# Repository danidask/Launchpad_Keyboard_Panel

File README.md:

# Specifications

- Size limit to the biggest size of low cost PCB manufacturers entry point PCBs (jlcpcb 100x100mm)
- Most of the components will be selected from https://jlcpcb.com/parts so they can be assembly by JLCPCB
- Other components will be sourced from cheap worldwide providers like aliexpress

See READMEs inside each folder

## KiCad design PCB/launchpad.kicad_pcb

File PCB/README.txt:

(see parent README.md)

# Requirements

Made with KiCad 6

## KiCad Plugins

https://github.com/bouni/kicad-jlcpcb-tools

# Track changes

[cadlab.io](https://cadlab.io/project/25849/)

# Specifications

(see parent README.md)

# Fabrication

The PCB is intended to be manufactured by JLCPCB so the outputs meet they requirements. Necessary files for manufacturing and assembly are in the jlcpcb folder

# BOM

LCSC parts are inside PCB\jlcpcb\assembly (to be assembly by jlcpcb or sourced from there and solder them manually)
- 12x Kailh choc Low profile Mechanical Switch, https://a.aliexpress.com/_uHRL47  (10 or 70)
- 12x Keycaps for Kailh choc, https://a.aliexpress.com/_uGXK51 (transparent-choc)
- 1x SSD1306 38x12mm OLED Display, https://a.aliexpress.com/_vNfBEr
- 1x RaspberryPi Pico, https://www.raspberrypi.com/products/raspberry-pi-pico/

# TODO

- Cover vias with soldermask
- Add diodes or limit resistors to keyboard matrix
- Power planes for 3.3v and 5v
- all pots (R1, R2, R3) swap GND and 3,3

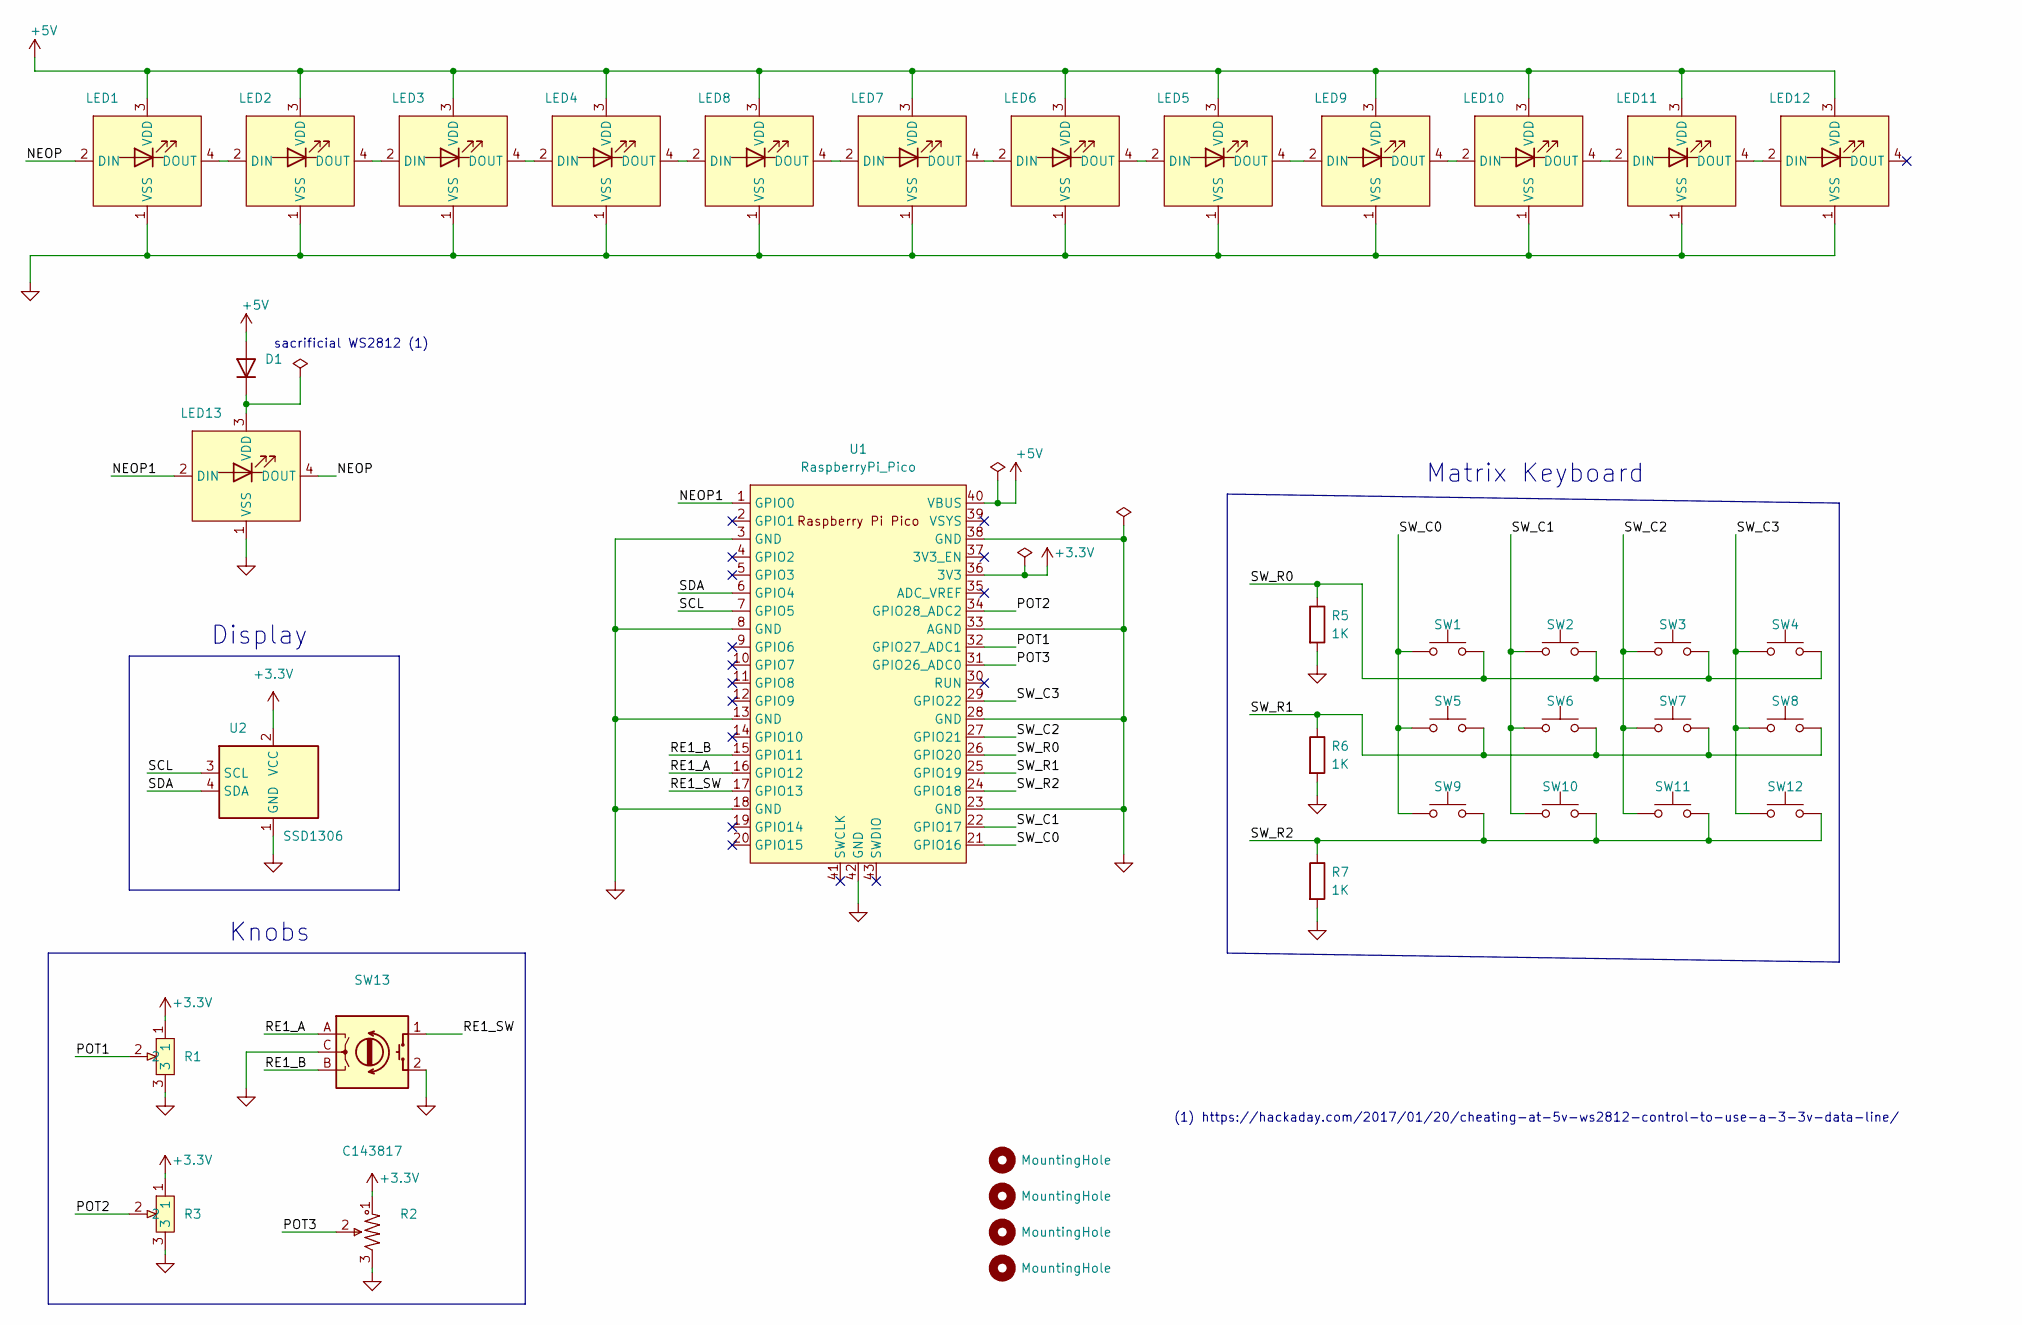
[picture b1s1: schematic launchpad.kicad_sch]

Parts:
D1: D; D_SOD-123F; MPN SM4007PL; LCSC C64898
H1, H2, H3, H4: MountingHole; MountingHole_3.2mm_M3
LED1, LED2, LED3, LED4, LED5, LED6, LED7, LED8, LED9, LED10, LED11, LED12, LED13: XL-3528RGBW-WS2812B; LED-SMD_4P-L3.5-W2.8-BR-1; LCSC Part C2890364
R1, R3: RDC1022A05; RES-ADJ-TH_RDC1022A05; LCSC Part C202389
R2: RK09K1130A6S; RES-TH_RK09K1130A6S; LCSC Part C209770
R5, R6, R7: 1K; R_0805_2012Metric_Pad1.20x1.40mm_HandSolder
SW1, SW2, SW3, SW4, SW5, SW6, SW7, SW8, SW9, SW10, SW11, SW12: Kaihua PG1350; Kaihua_PG1350
SW13: PEC11R-4220F-S0012; SW-TH_PEC11R-4220F-S0012; LCSC Part C143817
U1: RaspberryPi_Pico; RaspberryPi_Pico_SMD_TH
U2: SSD1306; SSD1306_38x12

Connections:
+3V3: R1.1, R2.1, R3.1, U1.36 (3V3), U2.2 (VCC)
+5V: D1.2 (A), LED1.3 (VDD), LED2.3 (VDD), LED3.3 (VDD), LED4.3 (VDD), LED5.3 (VDD), LED6.3 (VDD), LED7.3 (VDD), LED8.3 (VDD), LED9.3 (VDD), LED10.3 (VDD), LED11.3 (VDD), LED12.3 (VDD), U1.40 (VBUS)
/NEOP: LED1.2 (DIN), LED13.4 (DOUT)
/NEOP1: LED13.2 (DIN), U1.1 (GPIO0)
/POT1: R1.2, U1.32 (GPIO27_ADC1)
/POT2: R3.2, U1.34 (GPIO28_ADC2)
/POT3: R2.2, U1.31 (GPIO26_ADC0)
/RE1_A: SW13.A, U1.16 (GPIO12)
/RE1_B: SW13.B, U1.15 (GPIO11)
/RE1_SW: SW13.1 (S1), U1.17 (GPIO13)
/SCL: U1.7 (GPIO5), U2.3 (SCL)
/SDA: U1.6 (GPIO4), U2.4 (SDA)
/SW_C0: SW1.1 (A), SW5.1 (A), SW9.1 (A), U1.21 (GPIO16)
/SW_C1: SW2.1 (A), SW6.1 (A), SW10.1 (A), U1.22 (GPIO17)
/SW_C2: SW3.1 (A), SW7.1 (A), SW11.1 (A), U1.27 (GPIO21)
/SW_C3: SW4.1 (A), SW8.1 (A), SW12.1 (A), U1.29 (GPIO22)
/SW_R0: R5.1, SW1.2 (B), SW2.2 (B), SW3.2 (B), SW4.2 (B), U1.26 (GPIO20)
/SW_R1: R6.1, SW5.2 (B), SW6.2 (B), SW7.2 (B), SW8.2 (B), U1.25 (GPIO19)
/SW_R2: R7.1, SW9.2 (B), SW10.2 (B), SW11.2 (B), SW12.2 (B), U1.24 (GPIO18)
GND: LED1.1 (VSS), LED2.1 (VSS), LED3.1 (VSS), LED4.1 (VSS), LED5.1 (VSS), LED6.1 (VSS), LED7.1 (VSS), LED8.1 (VSS), LED9.1 (VSS), LED10.1 (VSS), LED11.1 (VSS), LED12.1 (VSS), LED13.1 (VSS), R1.3, R2.3, R3.3, R5.2, R6.2, R7.2, SW13.2 (S2), SW13.C, U1.3 (GND), U1.8 (GND), U1.13 (GND), U1.18 (GND), U1.23 (GND), U1.28 (GND), U1.33 (AGND), U1.38 (GND), U1.42 (GND), U2.1 (GND)
unnamed: D1.1 (K), LED13.3 (VDD)
unnamed: LED1.4 (DOUT), LED2.2 (DIN)
unnamed: LED2.4 (DOUT), LED3.2 (DIN)
unnamed: LED3.4 (DOUT), LED4.2 (DIN)
unnamed: LED4.4 (DOUT), LED8.2 (DIN)
unnamed: LED5.2 (DIN), LED6.4 (DOUT)
unnamed: LED5.4 (DOUT), LED9.2 (DIN)
unnamed: LED6.2 (DIN), LED7.4 (DOUT)
unnamed: LED7.2 (DIN), LED8.4 (DOUT)
unnamed: LED9.4 (DOUT), LED10.2 (DIN)
unnamed: LED10.4 (DOUT), LED11.2 (DIN)
unnamed: LED11.4 (DOUT), LED12.2 (DIN)

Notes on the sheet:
Knobs
sacrificial WS2812 (1)
Matrix Keyboard
Display
(1) https://hackaday.com/2017/01/20/cheating-at-5v-ws2812-control-to-use-a-3-3v-data-line/

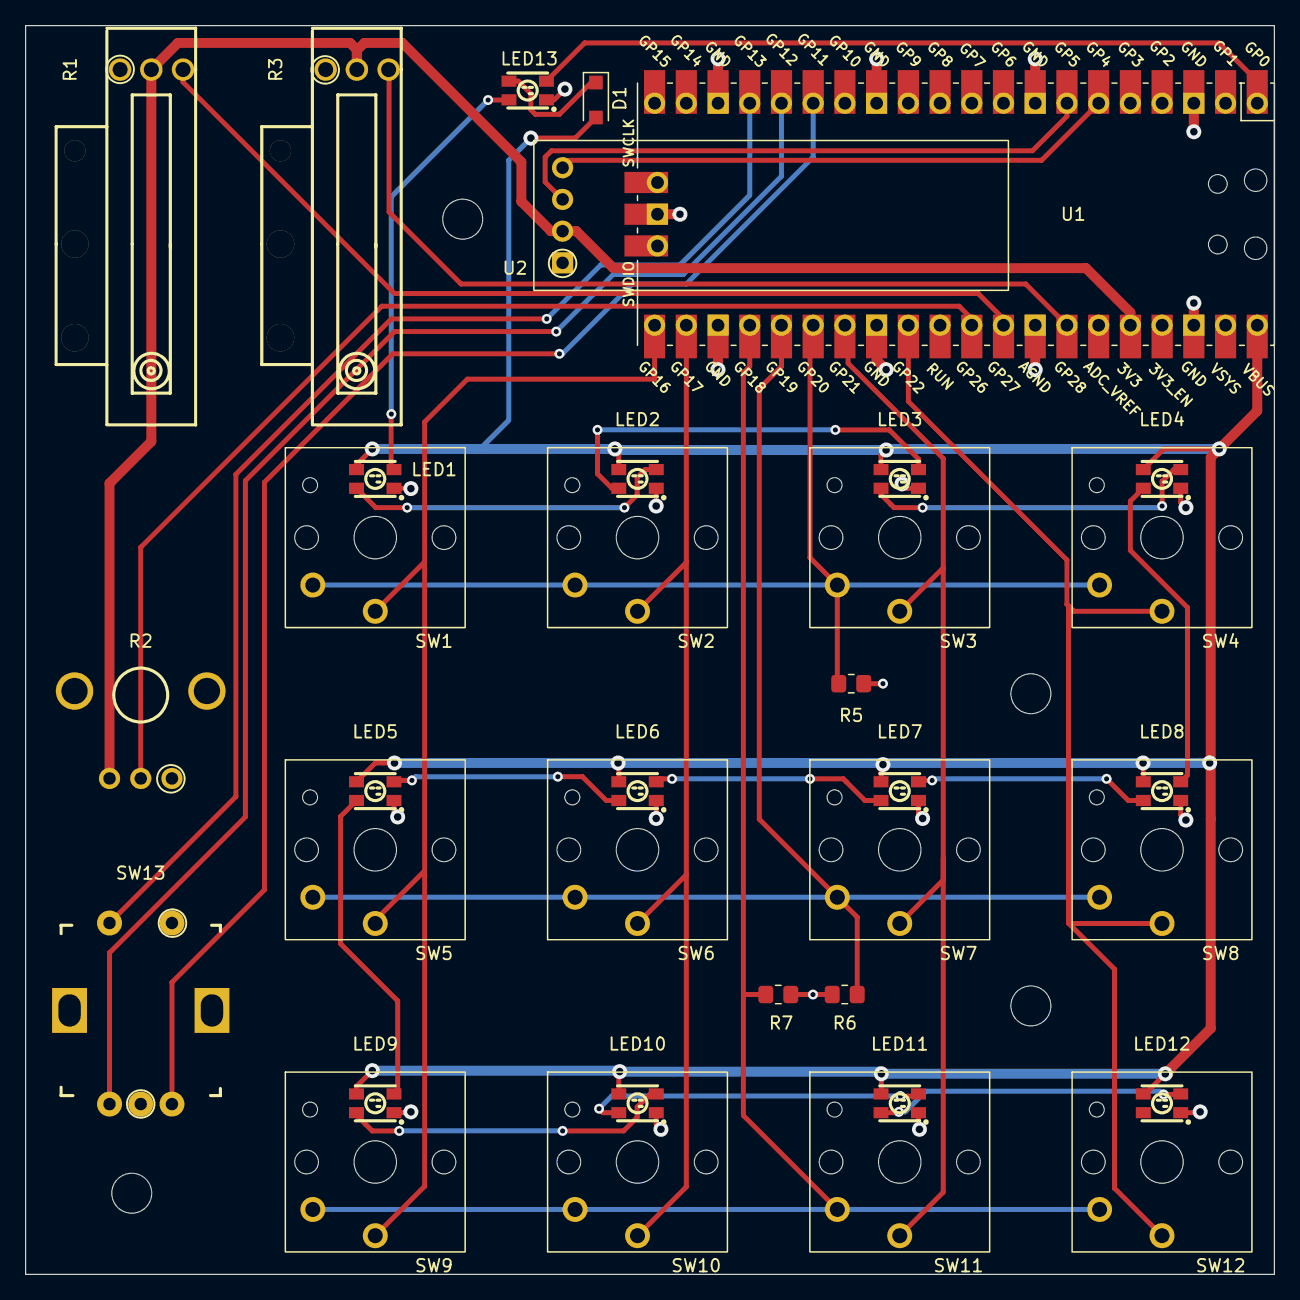
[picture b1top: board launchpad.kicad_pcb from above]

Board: 2 copper layers, 100.0 x 100.0 mm, 39 parts (0 on the bottom side), 32 nets.

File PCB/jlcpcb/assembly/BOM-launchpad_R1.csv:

Comment,Designator,Footprint,LCSC
PEC11R-4220F-S0012,SW13,SW-TH_PEC11R-4220F-S0012,C143817
1K,"R5,R6,R7",R_0805_2012Metric_Pad1.20x1.40mm_HandSolder,C17513
RDC1022A05,"R1,R3",RES-ADJ-TH_RDC1022A05,C202389
RK09K1130A6S,R2,RES-TH_RK09K1130A6S,C209770
XL-3528RGBW-WS2812B,"LED1,LED10,LED11,LED12,LED13,LED2,LED3,LED4,LED5,LED6,LED7,LED8,LED9",LED-SMD_4P-L3.5-W2.8-BR-1,C2890364
D,D1,D_SOD-123F,C64898
Kaihua PG1350,SW12,Kaihua_PG1350,
Kaihua PG1350,SW11,Kaihua_PG1350,
Kaihua PG1350,SW10,Kaihua_PG1350,
Kaihua PG1350,SW9,Kaihua_PG1350,
Kaihua PG1350,SW8,Kaihua_PG1350,
Kaihua PG1350,SW7,Kaihua_PG1350,
Kaihua PG1350,SW6,Kaihua_PG1350,
Kaihua PG1350,SW5,Kaihua_PG1350,
Kaihua PG1350,SW4,Kaihua_PG1350,
Kaihua PG1350,SW3,Kaihua_PG1350,
Kaihua PG1350,SW1,Kaihua_PG1350,
Kaihua PG1350,SW2,Kaihua_PG1350,
SSD1306,U2,SSD1306_38x12,
RaspberryPi_Pico,U1,RaspberryPi_Pico_SMD_TH,

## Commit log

2022-07-31 r1 almost finish
2022-07-31 R1 sent to fab
2022-07-31 rename library
2022-07-31 PCB 3D model
2022-08-07 gitignore
2022-08-07 cadlabio
2022-08-31 first firmware (no HID yet)
